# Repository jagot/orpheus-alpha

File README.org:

#+TITLE: Ορφέας Άλφα preamplifier
#+AUTHOR: Stefanos Carlström
#+EMAIL: stefanos.carlstrom@gmail.com

A simple preamplifier based around OPA2134 as buffer stage and PGA2311
as volume controller. A PSU (design [[https://www.muffsy.com/build-the-muffsy-psu-v3.html][courtesy of Muffsy]]) is also
present on the board, which is to be powered with 6VAC. Input signal
should be around Red Book standard.

[[./orpheus-alpha.pdf][Schematic]]

[[./images/front.png]]

[[./images/back.png]]

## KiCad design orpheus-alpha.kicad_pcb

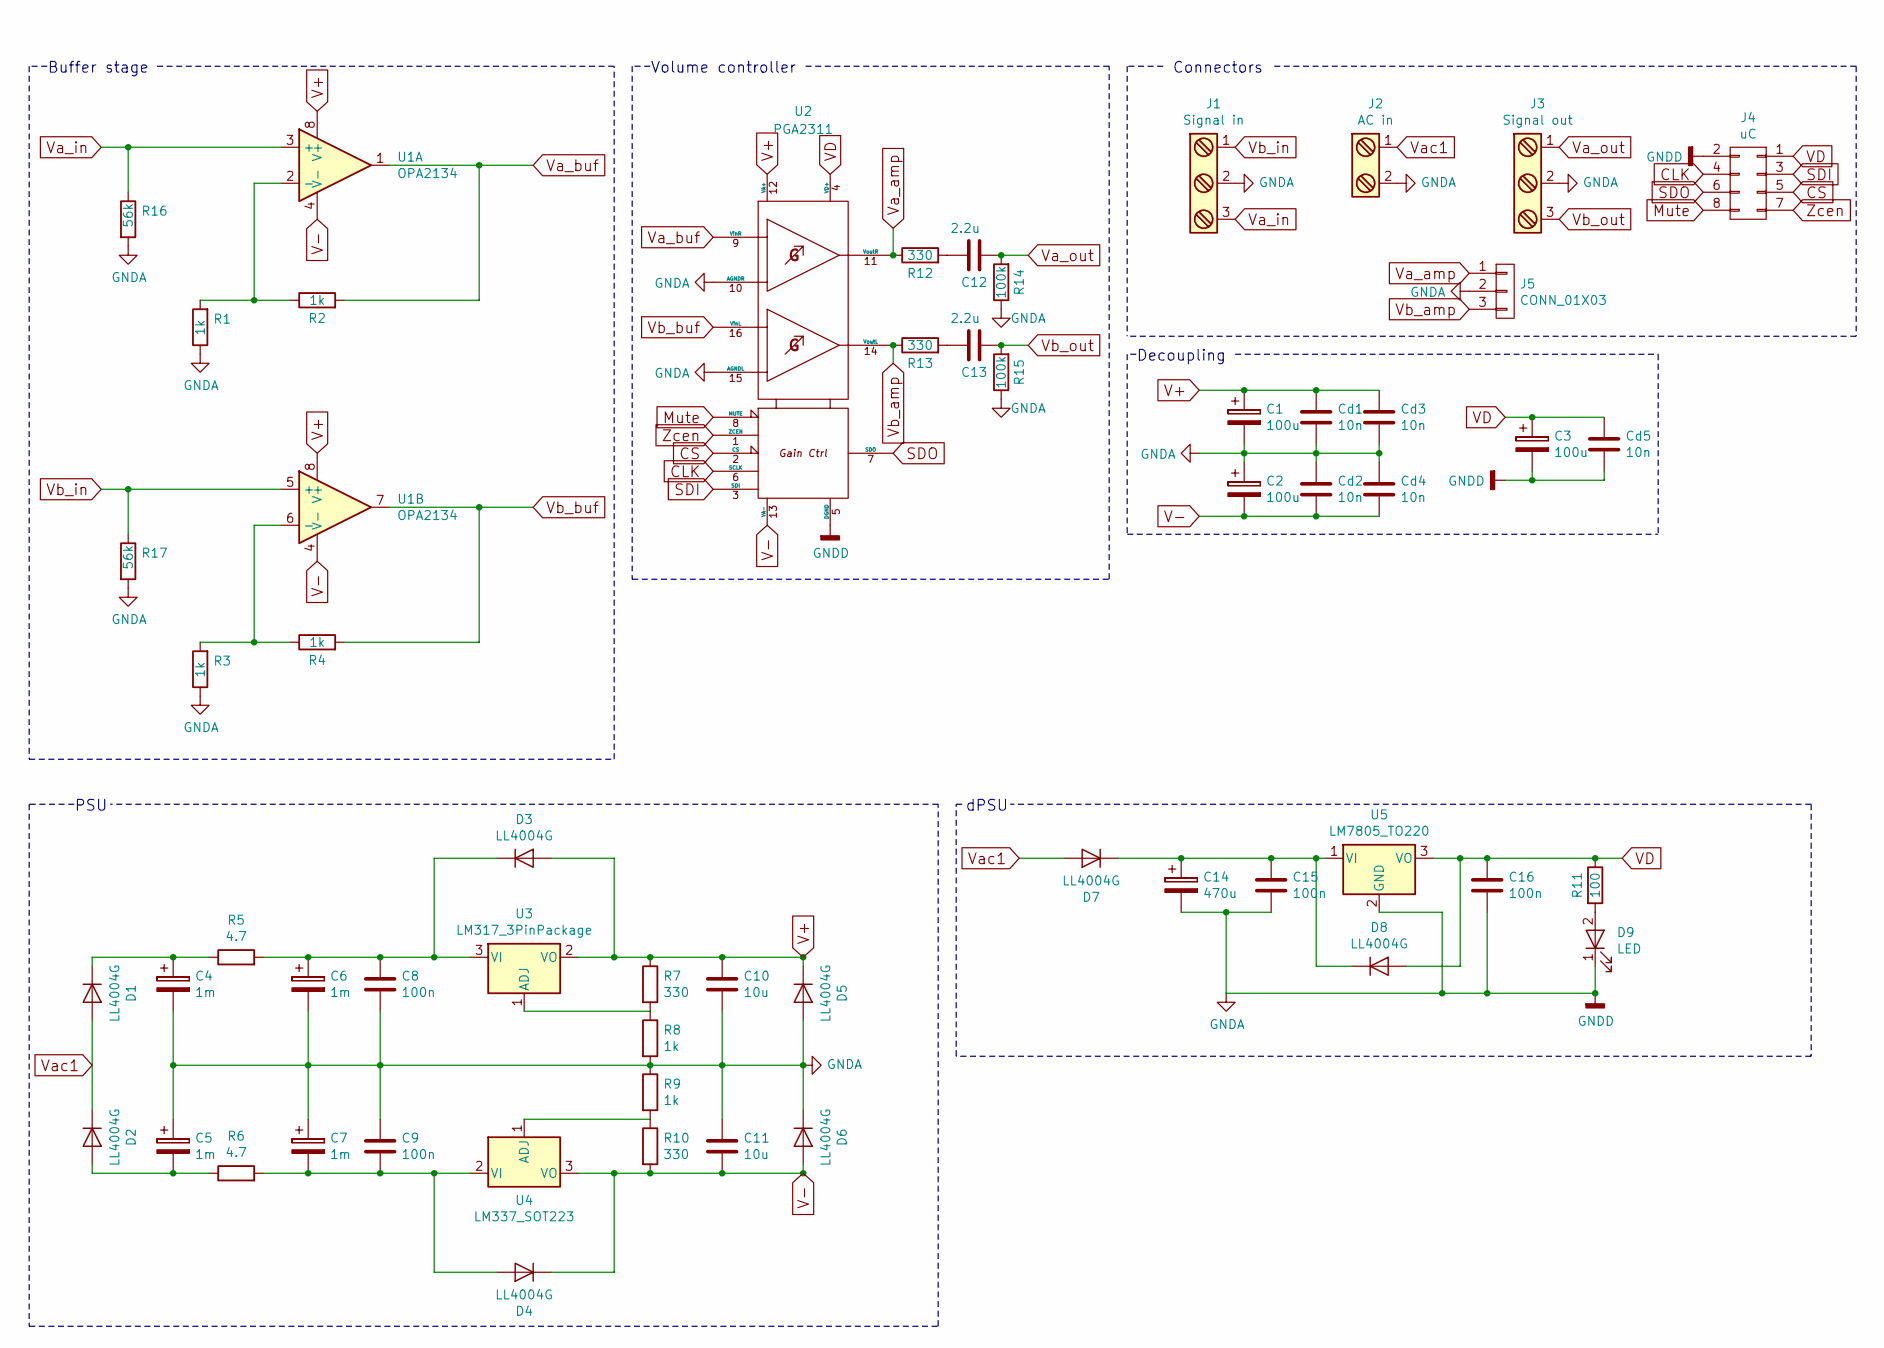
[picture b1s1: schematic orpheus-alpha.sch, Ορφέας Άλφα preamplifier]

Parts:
C1, C2, C3: 100u; CP_Radial_D5.0mm_P2.00mm; Voltage 16V
C4, C5, C6, C7: 1m; CP_Radial_D10.0mm_P5.00mm; Voltage 25V
C8, C9, C15, C16: 100n; C_0603_HandSoldering
C10, C11: 10u; C_0603_HandSoldering
C12, C13: 2.2u; C_Rect_L7.2mm_W7.2mm_P5.00mm_FKS2_FKP2_MKS2_MKP2
C14: 470u; CP_Radial_D10.0mm_P5.00mm; Voltage 25V
Cd1, Cd2, Cd3, Cd4, Cd5: 10n; C_0603_HandSoldering
D1, D2, D3, D4, D5, D6, D7, D8: LL4004G; D_MELF_Handsoldering
D9: LED; LED_0603_HandSoldering
J1: Signal in; TerminalBlock_Pheonix_MKDS1.5-3pol
J2: AC in; TerminalBlock_Pheonix_MKDS1.5-2pol
J3: Signal out; TerminalBlock_Pheonix_MKDS1.5-3pol
J4: uC; Pin_Header_Straight_2x04_Pitch2.54mm
J5: CONN_01X03; Pin_Header_Straight_1x03_Pitch2.54mm
R1, R2, R3, R4, R8, R9: 1k; R_0603_HandSoldering; Tolerance 1%
R5, R6: 4.7; R_1218_HandSoldering; Tolerance 1%
R7, R10, R12, R13: 330; R_0603_HandSoldering; Tolerance 1%
R11: 100; R_0603_HandSoldering; Tolerance 1%
R14, R15: 100k; R_0603_HandSoldering; Tolerance 1%
R16, R17: 56k; R_0603_HandSoldering; Tolerance 1%
U1: OPA2134; SOIC-8_3.9x4.9mm_Pitch1.27mm
U2: PGA2311; SOIC-16W_7.5x10.3mm_Pitch1.27mm
U3: LM317_3PinPackage; SOT-223-3Lead_TabPin2
U4: LM337_SOT223; SOT-223-3Lead_TabPin2
U5: LM7805_TO220; TO-220_Vertical

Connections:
CLK: J4.4, U2.6 (SCLK)
CS: J4.5, U2.2 (CS)
GNDA: C1.2, C2.1, C3.2, C4.2, C5.1, C6.2, C7.1, C8.2, C9.1, C10.2, C11.1, C14.2, C15.2, C16.2, Cd1.2, Cd2.1, Cd3.2, Cd4.1, Cd5.2, D5.2 (A), D6.1 (K), D9.1 (K), J1.2, J2.2, J3.2, J4.2, J5.2, R1.1, R3.1, R8.2, R9.1, R14.1, R15.1, R16.2, R17.2, U2.5 (DGND), U2.10 (AGNDR), U2.15 (AGNDL), U5.2 (GND)
Mute: J4.8, U2.8 (MUTE)
unnamed: C4.1, D1.1 (K), R5.1
unnamed: C5.2, D2.2 (A), R6.1
unnamed: C6.1, C8.1, D3.1 (K), R5.2, U3.3 (VI)
unnamed: C7.2, C9.2, D4.2 (A), R6.2, U4.2 (VI)
unnamed: C12.2, R12.2
unnamed: C13.2, R13.2
unnamed: C14.1, C15.1, D7.1 (K), D8.1 (K), U5.1 (VI)
unnamed: D9.2 (A), R11.2
unnamed: R1.2, R2.1, U1.2 (-)
unnamed: R3.2, R4.1, U1.6 (-)
unnamed: R7.2, R8.1, U3.1 (ADJ)
unnamed: R9.2, R10.1, U4.1 (ADJ)
SDI: J4.3, U2.3 (SDI)
SDO: J4.6, U2.7 (SDO)
V+: C1.1, C10.1, Cd1.1, Cd3.1, D3.2 (A), D5.1 (K), R7.1, U1.8 (V+), U2.12 (VA+), U3.2 (VO)
V-: C2.2, C11.2, Cd2.2, Cd4.2, D4.1 (K), D6.2 (A), R10.2, U1.4 (V-), U2.13 (VA-), U4.3 (VO)
VD: C3.1, C16.1, Cd5.1, D8.2 (A), J4.1, R11.1, U2.4 (VD+), U5.3 (VO)
Va_amp: J5.1, R12.1, U2.11 (VoutR)
Va_buf: R2.2, U1.1, U2.9 (VinR)
Va_in: J1.3, R16.1, U1.3 (+)
Va_out: C12.1, J3.1, R14.2
Vac1: D1.2 (A), D2.1 (K), D7.2 (A), J2.1
Vb_amp: J5.3, R13.1, U2.14 (VoutL)
Vb_buf: R4.2, U1.7, U2.16 (VinL)
Vb_in: J1.1, R17.1, U1.5 (+)
Vb_out: C13.1, J3.3, R15.2
Zcen: J4.7, U2.1 (ZCEN)

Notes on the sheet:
Decoupling
Buffer stage
Volume controller
Connectors
PSU
dPSU

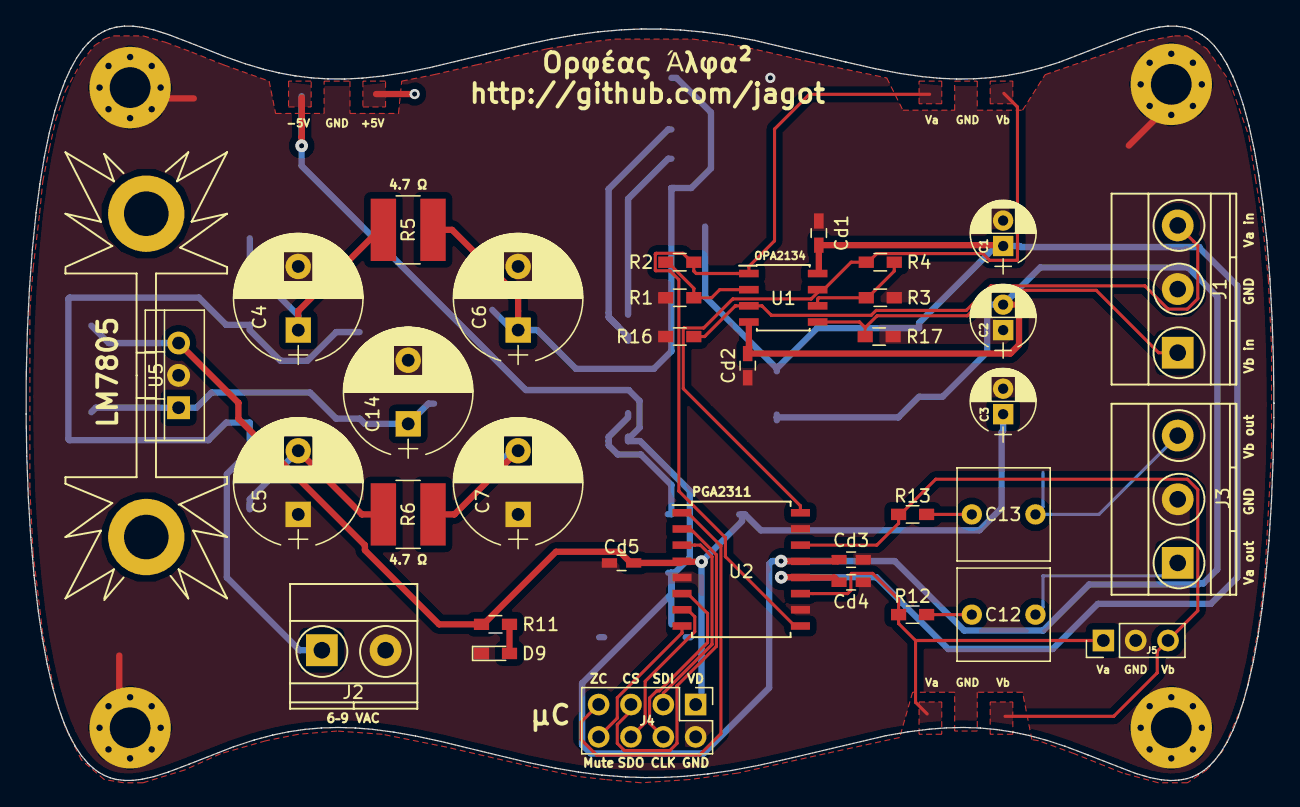
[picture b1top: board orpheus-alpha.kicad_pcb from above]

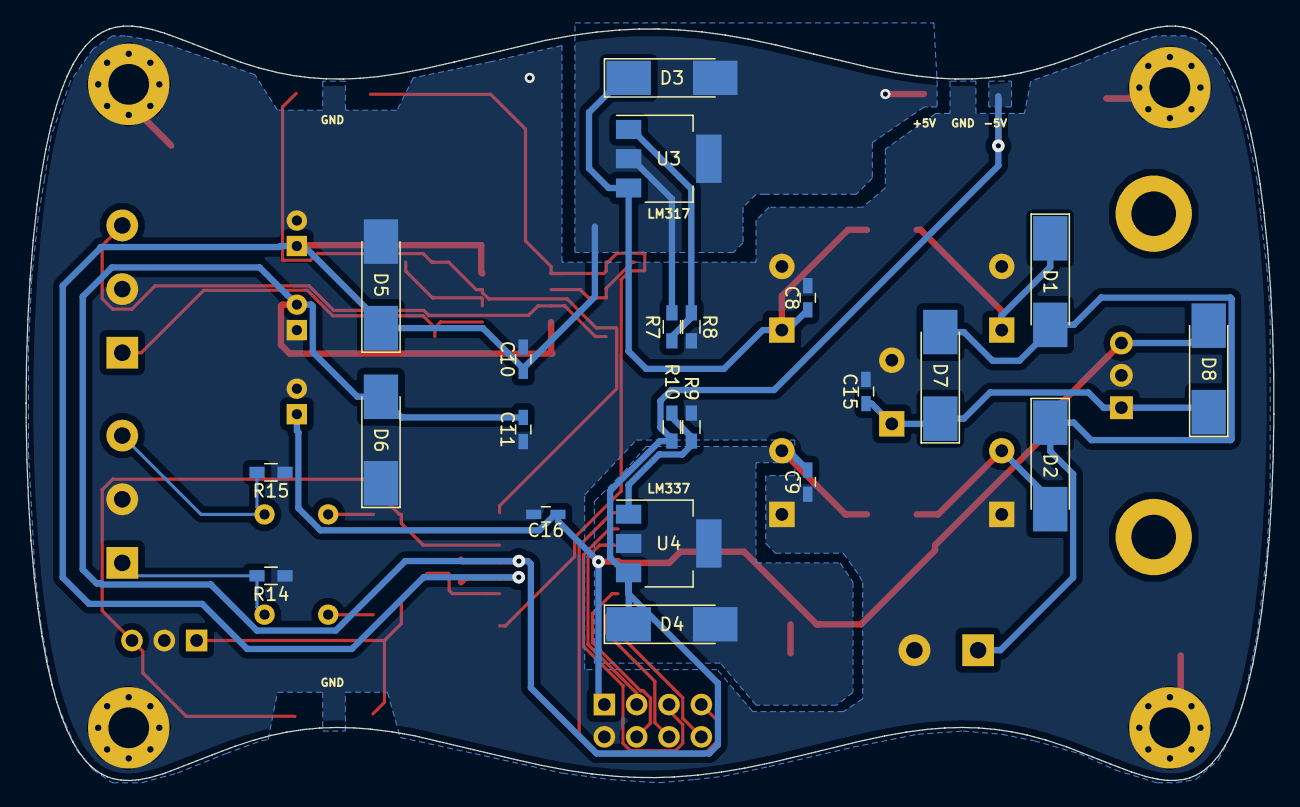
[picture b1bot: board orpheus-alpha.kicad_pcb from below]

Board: 2 copper layers, 98.0 x 59.3 mm, 57 parts (22 on the bottom side), 31 nets.

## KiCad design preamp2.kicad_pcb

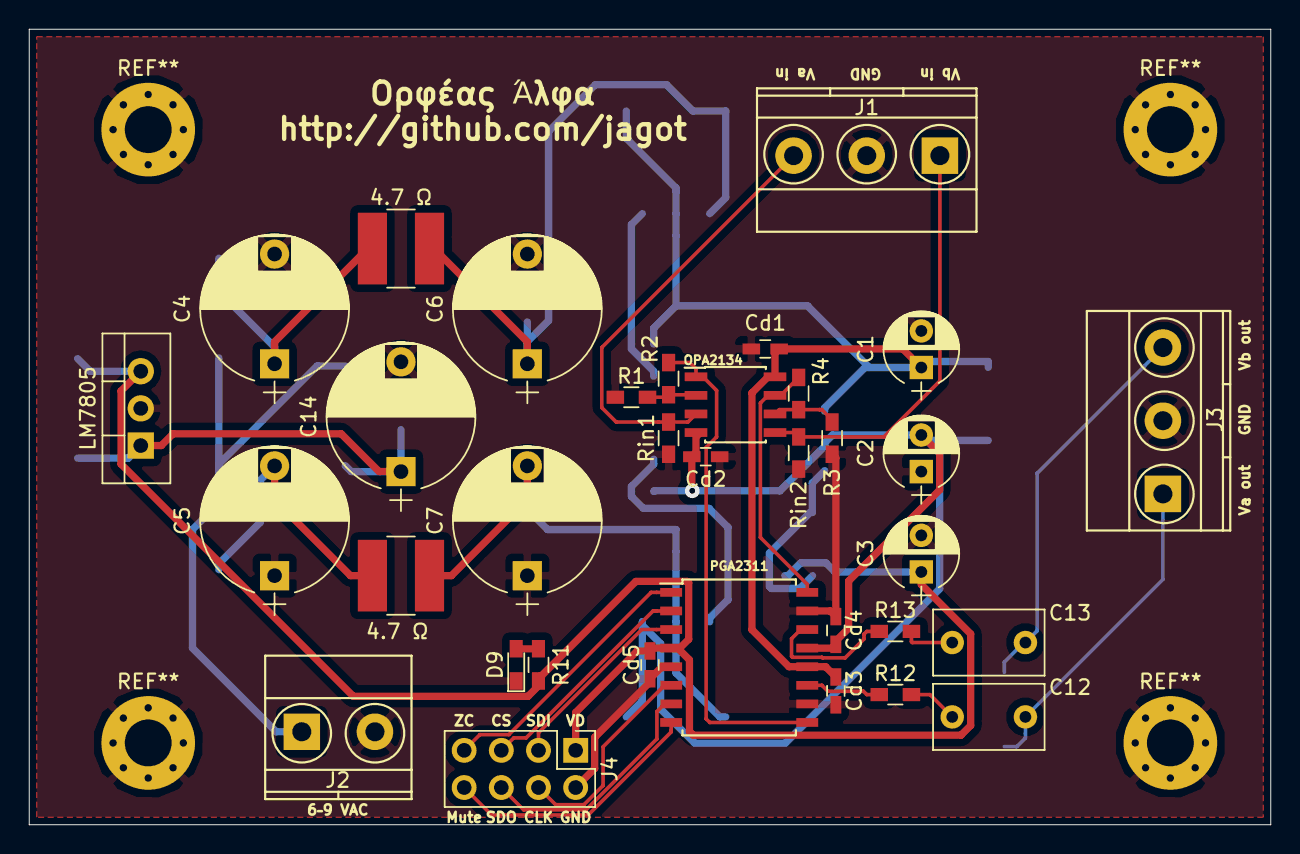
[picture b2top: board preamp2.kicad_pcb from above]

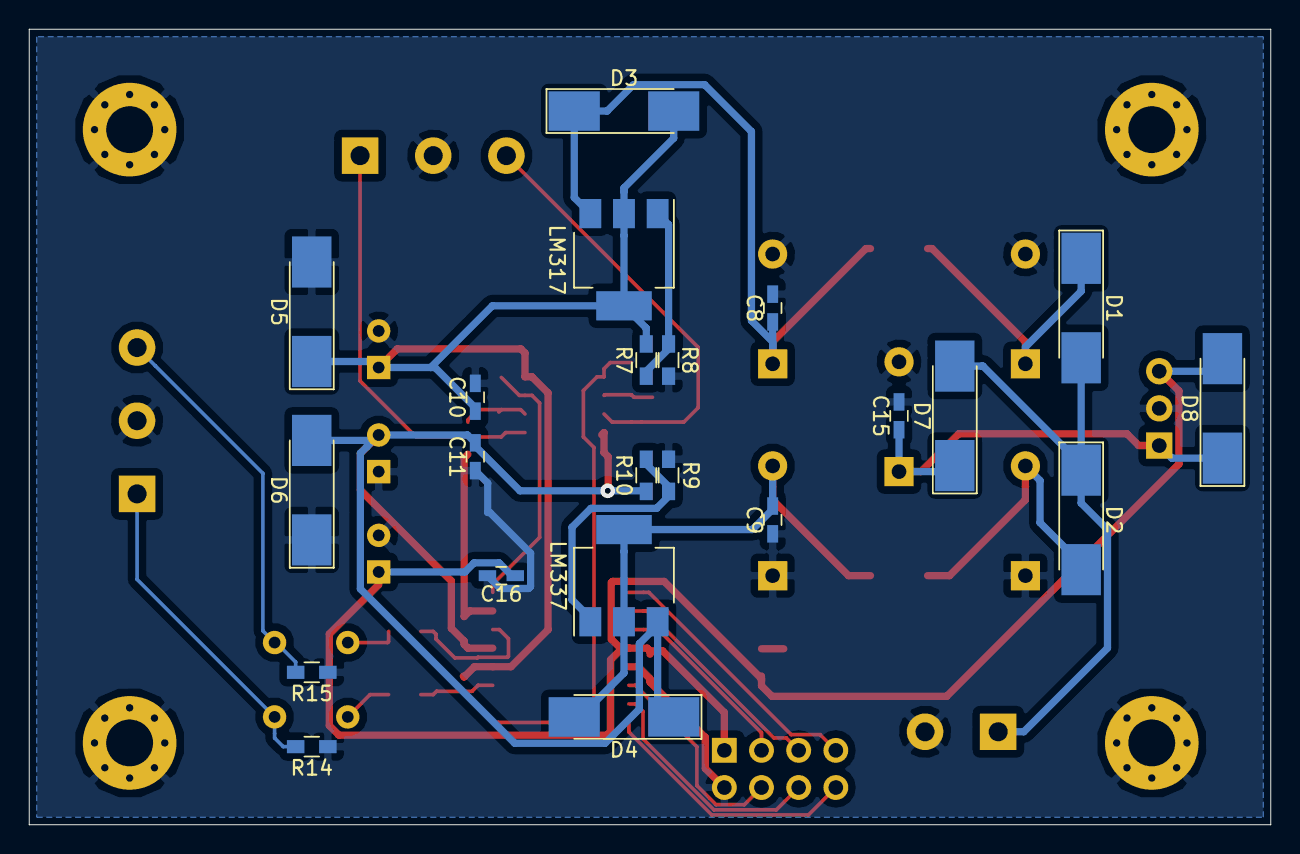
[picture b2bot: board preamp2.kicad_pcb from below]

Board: 2 copper layers, 84.8 x 54.4 mm, 56 parts (22 on the bottom side), 31 nets.

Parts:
4.7 Ω, 4.7 Ω#2: 4.7; R_1218_HandSoldering
C1, C2, C3: 100u; CP_Radial_D5.0mm_P2.50mm
C4, C5, C6, C7: 1m; CP_Radial_D10.0mm_P7.50mm
C8, C9, C15, C16: 100n; C_0603_HandSoldering
C10, C11: 10u; C_0603_HandSoldering
C12, C13: 2.2u; C_Disc_D7.5mm_W4.4mm_P5.00mm
C14: 470u; CP_Radial_D10.0mm_P7.50mm
Cd1, Cd2, Cd3, Cd4, Cd5: 10n; C_0603_HandSoldering
D1, D2, D3, D4, D5, D6, D7, D8: LL4004G; D_MELF_Handsoldering
D9: LED; LED_0603_HandSoldering
J1: Signal in; TerminalBlock_Pheonix_MKDS1.5-3pol
J2: AC in; TerminalBlock_Pheonix_MKDS1.5-2pol
J3: Signal out; TerminalBlock_Pheonix_MKDS1.5-3pol
J4: uC; Pin_Header_Straight_2x04_Pitch2.54mm
LM317: LM317_3PinPackage; SOT-223-3Lead_TabPin2
LM337: LM337_SOT223; SOT-223-3Lead_TabPin2
LM7805: LM7805_TO220; TO-220_Vertical
OPA2134: OPA2134; SOIC-8_3.9x4.9mm_Pitch1.27mm
PGA2311: PGA2311; SOIC-16W_7.5x10.3mm_Pitch1.27mm
R1, R2, R3, R4: 1k; R_0603_HandSoldering
R7, R10: 910; R_0603_HandSoldering
R8, R9: 2k7; R_0603_HandSoldering
R11: 100; R_0603_HandSoldering
R12, R13: 300; R_0603_HandSoldering
R14, R15: 100k; R_0603_HandSoldering
Rin1, Rin2: 56k; R_0603_HandSoldering

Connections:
CLK: J4.4, PGA2311.6
CS: J4.5, PGA2311.2
GNDA: C1.2, C2.1, C3.2, C4.2, C5.1, C6.2, C7.1, C8.2, C9.1, C10.2, C11.1, C14.2, C15.2, C16.2, Cd1.2, Cd2.1, Cd3.2, Cd4.1, Cd5.2, D5.2, D6.1, D9.1, J1.2, J2.2, J3.2, J4.2, LM7805.2, PGA2311.5, PGA2311.10, PGA2311.15, R1.1, R3.1, R8.2, R9.1, R14.1, R15.1, Rin1.2, Rin2.2
Mute: J4.8, PGA2311.8
unnamed: 4.7 Ω.1, C4.1, D1.1
unnamed: 4.7 Ω#2.1, C5.2, D2.2
unnamed: 4.7 Ω.2, C6.1, C8.1, D3.1, LM317.3
unnamed: 4.7 Ω#2.2, C7.2, C9.2, D4.2, LM337.2
unnamed: C12.2, R12.2
unnamed: C13.2, R13.2
unnamed: C14.1, C15.1, D7.1, D8.1, LM7805.1
unnamed: D9.2, R11.2
unnamed: OPA2134.2, R1.2, R2.1
unnamed: OPA2134.6, R3.2, R4.1
unnamed: LM317.1, R7.2, R8.1
unnamed: LM337.1, R9.2, R10.1
unnamed: PGA2311.11, R12.1
unnamed: PGA2311.14, R13.1
SDI: J4.3, PGA2311.3
SDO: J4.6, PGA2311.7
V+: C1.1, C10.1, Cd1.1, Cd3.1, D3.2, D5.1, LM317.2, OPA2134.8, PGA2311.12, R7.1
V-: C2.2, C11.2, Cd2.2, Cd4.2, D4.1, D6.2, LM337.3, OPA2134.4, PGA2311.13, R10.2
VD: C3.1, C16.1, Cd5.1, D8.2, J4.1, LM7805.3, PGA2311.4, R11.1
Va_buf: OPA2134.1, PGA2311.9, R2.2
Va_in: J1.3, OPA2134.3, Rin1.1
Va_out: C12.1, J3.1, R14.2
Vac1: D1.2, D2.1, D7.2, J2.1
Vb_buf: OPA2134.7, PGA2311.16, R4.2
Vb_in: J1.1, OPA2134.5, Rin2.1
Vb_out: C13.1, J3.3, R15.2
Zcen: J4.7, PGA2311.1

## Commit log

2017-09-16 Decreased resistor value to increase possible current
2017-09-17 Increased pin header size
2017-09-17 Added some silk screen annotations
2017-09-17 Renamed project
2017-09-17 Updated schematic
2017-09-18 Small changes, changed output coupling caps to film type
2017-09-18 Added part numbers
2017-09-27 Changed some part values and part numbers
2017-10-15 Added optional power connectors
2018-03-31 New layout, "debug" connection pads at the edge
2018-04-01 Added heatsinks
2018-04-01 Changed footprint of PSU capacitors
